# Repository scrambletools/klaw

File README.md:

# KLAW - 34-key split keyboard

KLAW is a compact **34-key split keyboard with LEDs, OLED, buzzer and
encoder**. It is designed as one reversible PCB that serves both halves -
components on the back face make the right half, components on the front face
make the left half. One board design: the same gerber files can be used for
both halves, with separate BOM and CPL files per half. Every component can be
machine-assembled, but you may want to hand-assemble the MCU and OLED modules.
The latest hardware revision is rev 2.

Below are renders of the right half:

## Features

- **34 keys** (17 per half), column-staggered, MX-style switches
- **Hot-swap sockets** (Kailh CPG151101S11-compatible) - no switch soldering
- **Per-key RGB** - SK6812MINI-EA LEDs, reverse-mounted to glow through the board (machine-assemblable)
- **Wired or wireless** - TRRS between halves, or Bluetooth with a
  nice!nano-compatible controller (socketed, Pro Micro pinout); battery
  connector and power switch on board (unpopulated in the wired-first default)
- **Rotary encoder** (EC11) per half - volume knob or anything you map to it
- **0.96″ SSD1306 OLED** per half
- **Piezo buzzer**, reset button, and optional
  [splitkb tenting puck](https://splitkb.com/products/tenting-puck) mounting
- **Optional trackball** level-converter header (unpopulated by default)
- **Configuration by placement** - the OLED mapping, trackball routing, and
  battery-polarity links are 0603 0R resistors, placed per side by the
  assembly service; nothing to bridge by hand

## Repository layout

| Path | Contents |
|---|---|
| `pcb/klaw_2/` | KiCad 10 project - schematic, board, project library with LCSC sourcing fields and 3D models |
| `fab/` | JLCPCB production files - gerbers, drills, BOM, placement (see `fab/README.md`) |
| `bom/` | Per-half build BOMs (`bom_left.csv`, `bom_right.csv`) with LCSC part numbers |
| - | Firmware (QMK/Vial) lives in [scrambletools/klaw-firmware](https://github.com/scrambletools/klaw-firmware) |

The case is designed in Plasticity and maintained outside this repository.

## Building one

**1. Order the PCBs.** Both halves use the **same board** - upload
`fab/klaw_2-gerbers.zip` to [JLCPCB](https://jlcpcb.com) (2-layer, 1.6 mm). For
machine assembly place **two orders with the same gerbers**: the right half
assembles on the **Bottom** side (`fab/right-half/`), the left half on the
**Top** side (`fab/left-half/`). Each order is double-sided and covers everything
solderable - see `fab/README.md` for the exact flow and placement-review checklist.

**2. No soldering required** - the assembly orders cover everything solderable:
diodes, factory-reversed per-key RGB LEDs (SK6812MINI-EA), hot-swap sockets,
TRRS, buzzer, reset switch, encoder, and each side's 0R configuration resistors
(double-sided assembly: the buzzer and encoder mount on the keycap face, every
other machine-placed part on the component face).
Mount-face tables, part numbers, prices, and per-half quantities are in `bom/`.

**3. Add your own** MX-style switches (hot-swap, no soldering), a
nice!nano-compatible controller (socket it - the MCU mounts on the **bottom**,
components facing the PCB, as marked on the silkscreen), a 4-pin I²C SSD1306
OLED module, and keycaps. For a wireless build, additionally fit the power
switch (`C431540`), JST battery connector (`C173752`), and a 301230-or-similar
LiPo - those three positions are DNP in the wired-first default, but their
polarity-selection resistors are already placed correctly per side.

**4. Firmware.** Flash the KLAW firmware (QMK/Vial) from
[scrambletools/klaw-firmware](https://github.com/scrambletools/klaw-firmware).

The KiCad project embeds datasheet links, LCSC part numbers, and last-checked
stock/pricing on every schematic symbol, so `kicad-cli sch export bom` always
gives you a current shopping list.

## Credits & license

KLAW is a derivative of the [KLOR](https://github.com/GEIGEIGEIST/KLOR)
keyboard by GEIGEIGEIST - the layout, reversible-footprint approach, and much
of the PCB heritage come from that project. Licensed under **GPL-3.0**, same
as KLOR; see `LICENSE.md`. The Cherry MX switch 3D model comes from the
[kiswitch keyswitch-kicad-library](https://github.com/kiswitch/keyswitch-kicad-library)
(MIT / CC-BY-SA 4.0); the nRF52840 SuperMini controller model comes from
[shnaps/garden36](https://github.com/shnaps/garden36) (MIT).

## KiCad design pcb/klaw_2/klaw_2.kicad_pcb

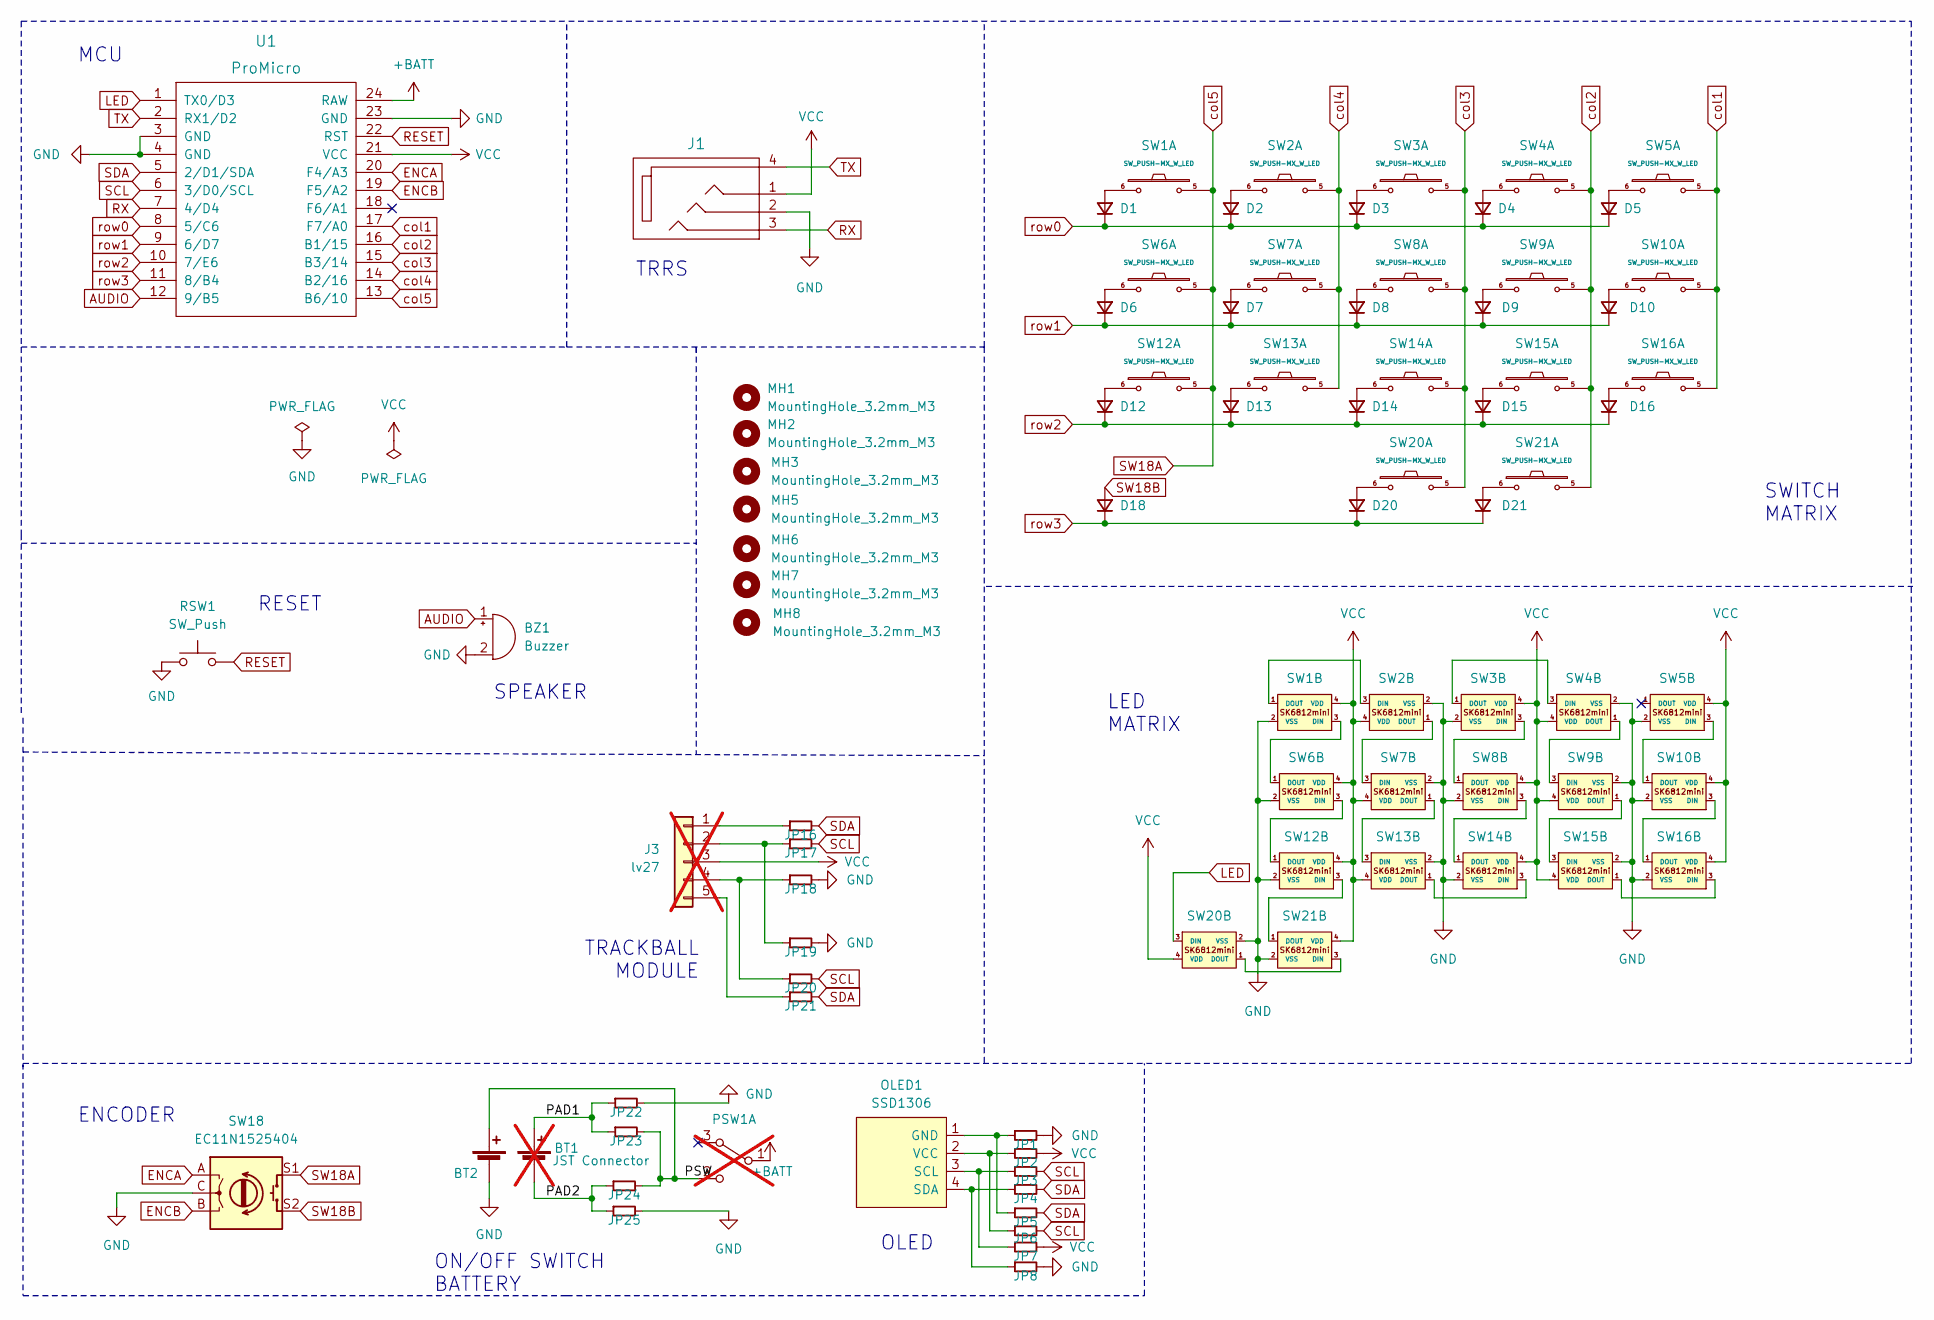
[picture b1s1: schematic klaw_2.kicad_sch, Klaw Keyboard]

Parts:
BT1: JST Connector; JST_PH_reversible; LCSC C173752; not fitted
BT2: Battery_Cell; custombatteryconnector_small
BZ1: Buzzer; Buzzer_Mallory_AST1109MLTRQ_reversible; LCSC C201047
D1, D2, D3, D4, D5, D6, D7, D8, D9, D10, D12, D13, D14, D15, D16, D18, D20, D21: 1N4148W; Diode_SOD123; LCSC C81598
J1: PJ-320A-4P; MJ-4PP-9; MPN PJ-320A-4P; LCSC C18185602
J3: lv27; lvc27_onlyInput; not fitted
JP1, JP2, JP3, JP4, JP5, JP6, JP7, JP8, JP16, JP17, JP18, JP19, JP20, JP21, JP22, JP23, JP24, JP25: 0R; R_0603_1608Metric; MPN 0603WAF0000T5E; LCSC C21189
MH1, MH2, MH3, MH5, MH6, MH7, MH8: MountingHole_3.2mm_M3
OLED1: SSD1306; SSD1306_128x64OLED
PSW1: SW_DPDT_x2; MSK12C02_reversible; LCSC C431540; not fitted
RSW1: SW_Push; SW_Push_1P1T-MP_NO_Horizontal_Alps_SKRTLAE010_both_sides; LCSC C110293
SW1, SW2, SW3, SW4, SW5, SW6, SW7, SW8, SW9, SW10, SW12, SW13, SW14, SW15, SW16, SW20, SW21: SW_PUSH-MX_W_LED; SK6812MINI_and_cherry; MPN SK6812MINI-EA; LCSC C5378731
SW18: EC11N1525404; RotaryEncoder_Alps_EC11E-Switch_Vertical_H20mm-keebio_modif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; MPN EC11N1525404; LCSC C470748
U1: ProMicro

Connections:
+BATT: PSW1.1 (B), U1.24 (RAW)
/PAD1: BT1.1 (+), JP22.1, JP23.1
/PAD2: BT1.2 (-), JP24.1, JP25.1
/PSW: BT2.1 (+), JP23.2, JP24.2, PSW1.2 (C)
AUDIO: BZ1.1 (-), U1.12 (9/B5)
ENCA: SW18.A, U1.20 (F4/A3)
ENCB: SW18.B, U1.19 (F5/A2)
GND: BT2.2 (-), BZ1.2 (+), J1.2, JP1.2, JP8.2, JP18.2, JP19.2, JP22.2, JP25.2, RSW1.1, SW1.2 (VSS), SW2.2 (VSS), SW3.2 (VSS), SW4.2 (VSS), SW5.2 (VSS), SW6.2 (VSS), SW7.2 (VSS), SW8.2 (VSS), SW9.2 (VSS), SW10.2 (VSS), SW12.2 (VSS), SW13.2 (VSS), SW14.2 (VSS), SW15.2 (VSS), SW16.2 (VSS), SW18.C, SW20.2 (VSS), SW21.2 (VSS), U1.3 (GND), U1.4 (GND), U1.23 (GND)
LED: SW20.3 (DIN), U1.1 (TX0/D3)
unnamed: D1.2 (A), SW1.6
unnamed: D2.2 (A), SW2.6
unnamed: D3.2 (A), SW3.6
unnamed: D4.2 (A), SW4.6
unnamed: D5.2 (A), SW5.6
unnamed: D6.2 (A), SW6.6
unnamed: D7.2 (A), SW7.6
unnamed: D8.2 (A), SW8.6
unnamed: D9.2 (A), SW9.6
unnamed: D10.2 (A), SW10.6
unnamed: D12.2 (A), SW12.6
unnamed: D13.2 (A), SW13.6
unnamed: D14.2 (A), SW14.6
unnamed: D15.2 (A), SW15.6
unnamed: D16.2 (A), SW16.6
unnamed: D20.2 (A), SW20.6
unnamed: D21.2 (A), SW21.6
unnamed: J3.1, JP16.1
unnamed: J3.2, JP17.1, JP19.1
unnamed: J3.4, JP18.1, JP20.1
unnamed: J3.5, JP21.1
unnamed: JP1.1, JP5.1, OLED1.1 (GND)
unnamed: JP3.1, JP7.1, OLED1.3 (SCL)
unnamed: JP4.1, JP8.1, OLED1.4 (SDA)
unnamed: JP2.1, JP6.1, OLED1.2 (VCC)
unnamed: SW1.3 (DIN), SW6.1 (DOUT)
unnamed: SW1.1 (DOUT), SW2.3 (DIN)
unnamed: SW2.1 (DOUT), SW7.3 (DIN)
unnamed: SW3.3 (DIN), SW8.1 (DOUT)
unnamed: SW3.1 (DOUT), SW4.3 (DIN)
unnamed: SW4.1 (DOUT), SW9.3 (DIN)
unnamed: SW10.3 (DIN), SW16.1 (DOUT)
unnamed: SW5.3 (DIN), SW10.1 (DOUT)
unnamed: SW12.3 (DIN), SW21.1 (DOUT)
unnamed: SW6.3 (DIN), SW12.1 (DOUT)
unnamed: SW7.1 (DOUT), SW13.3 (DIN)
unnamed: SW13.1 (DOUT), SW14.3 (DIN)
unnamed: SW8.3 (DIN), SW14.1 (DOUT)
unnamed: SW9.1 (DOUT), SW15.3 (DIN)
unnamed: SW15.1 (DOUT), SW16.3 (DIN)
unnamed: SW20.1 (DOUT), SW21.3 (DIN)
RESET: RSW1.2, U1.22 (RST)
RX: J1.3, U1.7 (4/D4)
SCL: JP3.2, JP6.2, JP17.2, JP20.2, U1.6 (3/D0/SCL)
SDA: JP4.2, JP5.2, JP16.2, JP21.2, U1.5 (2/D1/SDA)
SW18A: SW1.5, SW6.5, SW12.5, SW18.S1, U1.13 (B6/10)
SW18B: D18.2 (A), SW18.S2
TX: J1.4, U1.2 (RX1/D2)
VCC: J1.1, J3.3, JP2.2, JP7.2, SW1.4 (VDD), SW2.4 (VDD), SW3.4 (VDD), SW4.4 (VDD), SW5.4 (VDD), SW6.4 (VDD), SW7.4 (VDD), SW8.4 (VDD), SW9.4 (VDD), SW10.4 (VDD), SW12.4 (VDD), SW13.4 (VDD), SW14.4 (VDD), SW15.4 (VDD), SW16.4 (VDD), SW20.4 (VDD), SW21.4 (VDD), U1.21 (VCC)
col1: SW5.5, SW10.5, SW16.5, U1.17 (F7/A0)
col2: SW4.5, SW9.5, SW15.5, SW21.5, U1.16 (B1/15)
col3: SW3.5, SW8.5, SW14.5, SW20.5, U1.15 (B3/14)
col4: SW2.5, SW7.5, SW13.5, U1.14 (B2/16)
row0: D1.1 (K), D2.1 (K), D3.1 (K), D4.1 (K), D5.1 (K), U1.8 (5/C6)
row1: D6.1 (K), D7.1 (K), D8.1 (K), D9.1 (K), D10.1 (K), U1.9 (6/D7)
row2: D12.1 (K), D13.1 (K), D14.1 (K), D15.1 (K), D16.1 (K), U1.10 (7/E6)
row3: D18.1 (K), D20.1 (K), D21.1 (K), U1.11 (8/B4)

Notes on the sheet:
SWITCH MATRIX
MCU
ON/OFF SWITCH BATTERY
ENCODER
OLED
LED MATRIX
TRRS
TRACKBALL MODULE
RESET
SPEAKER

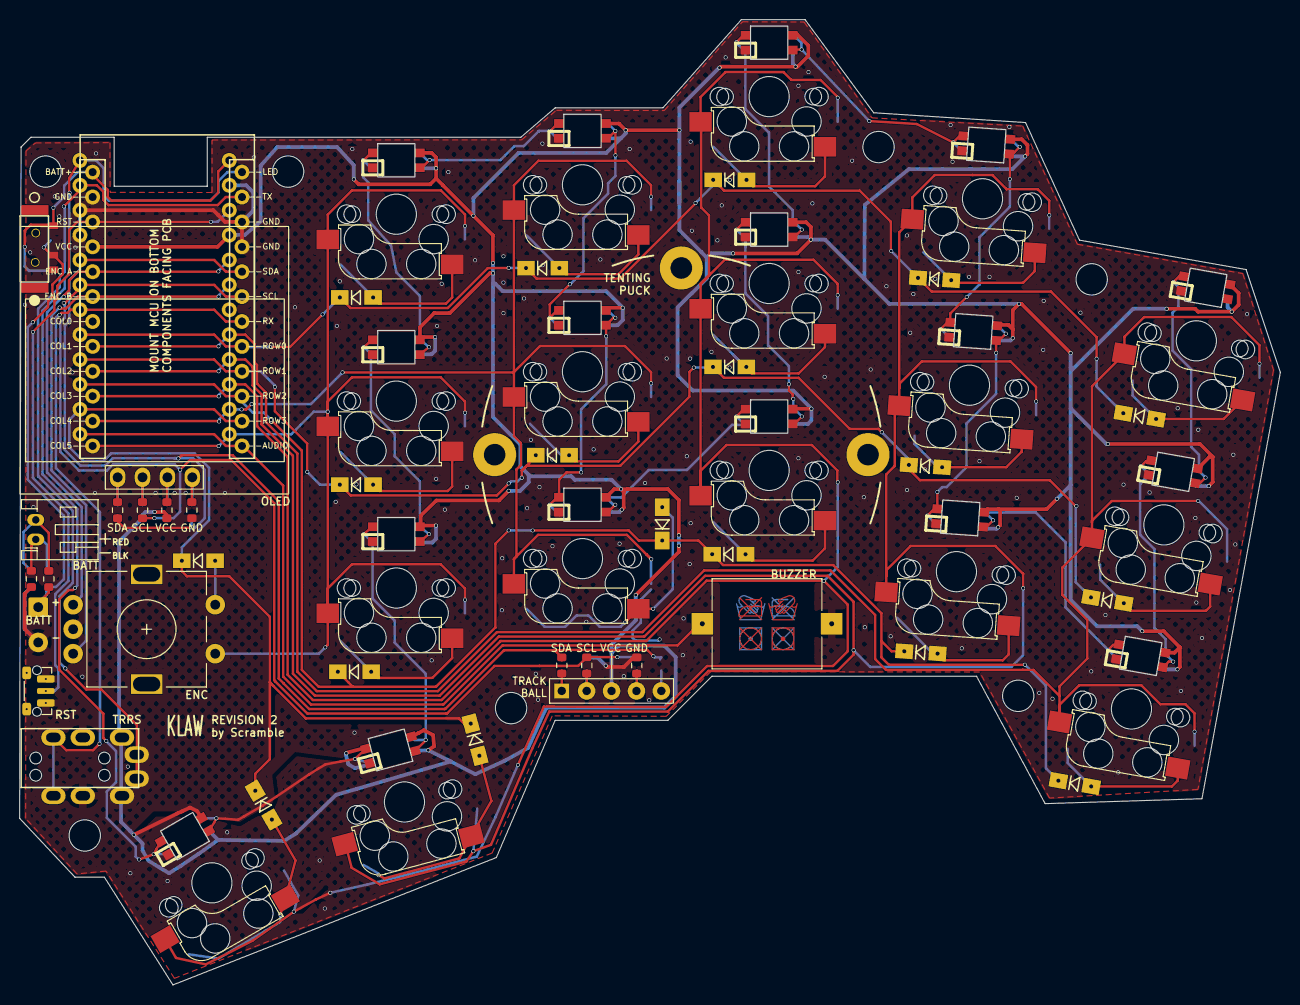
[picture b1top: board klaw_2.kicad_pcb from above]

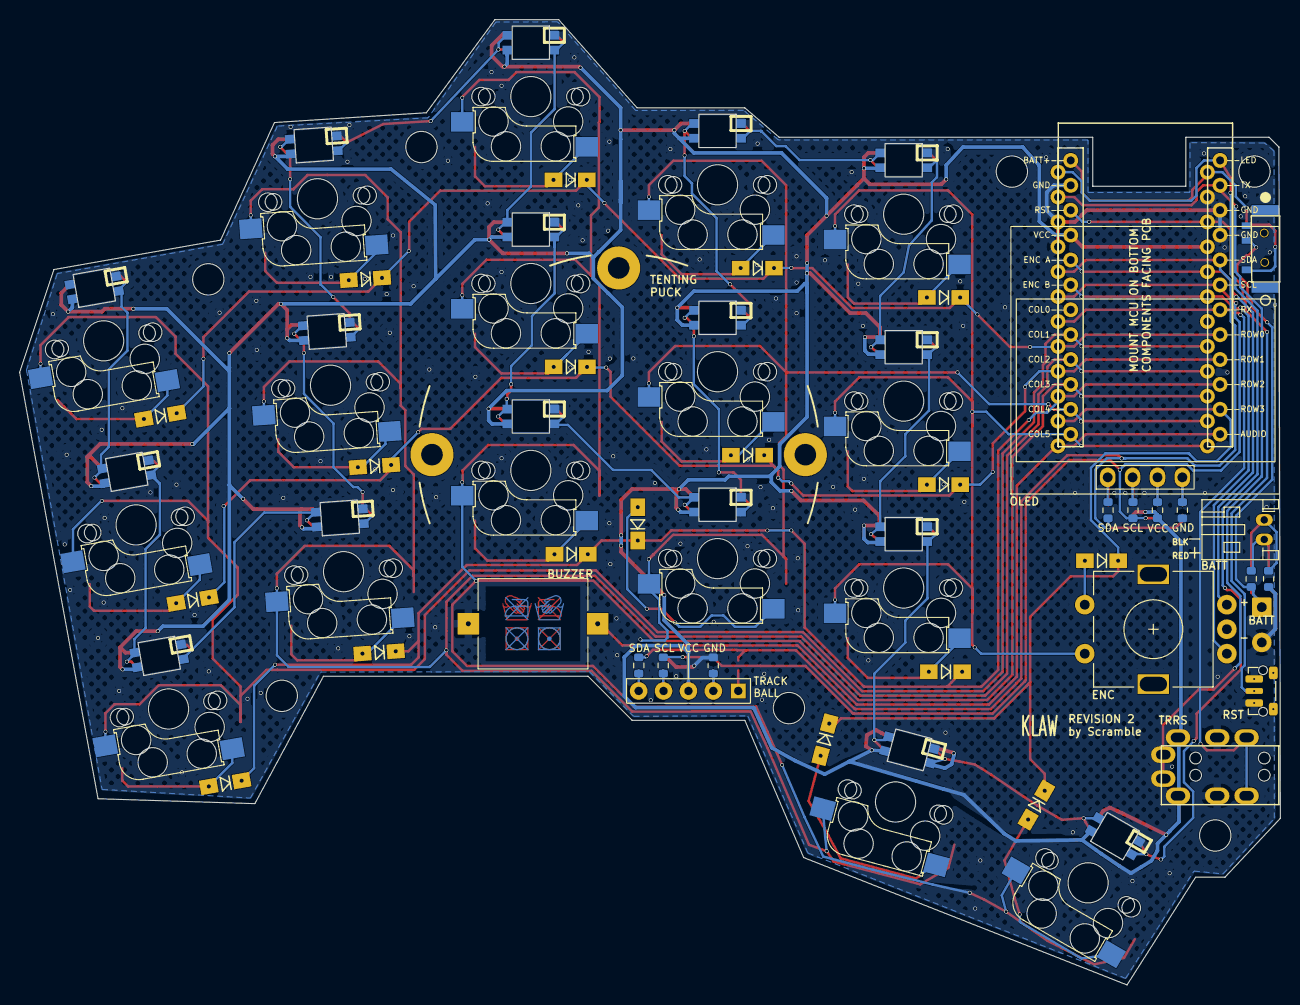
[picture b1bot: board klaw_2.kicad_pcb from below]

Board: 2 copper layers, 128.6 x 98.5 mm, 70 parts (9 on the bottom side), 66 nets.
